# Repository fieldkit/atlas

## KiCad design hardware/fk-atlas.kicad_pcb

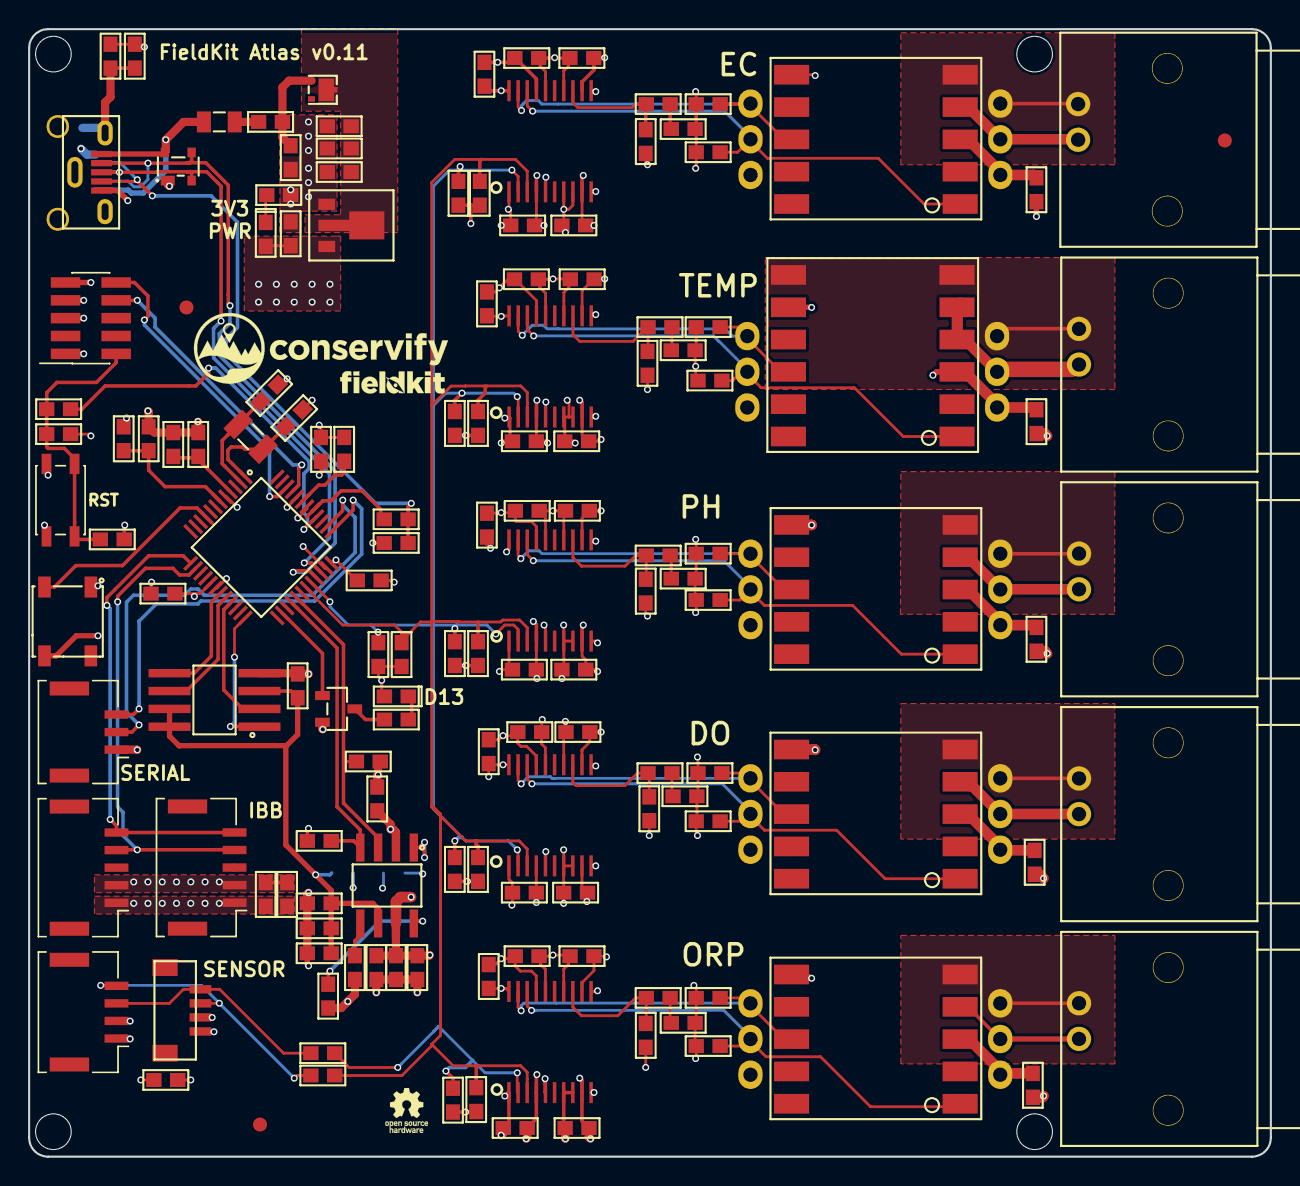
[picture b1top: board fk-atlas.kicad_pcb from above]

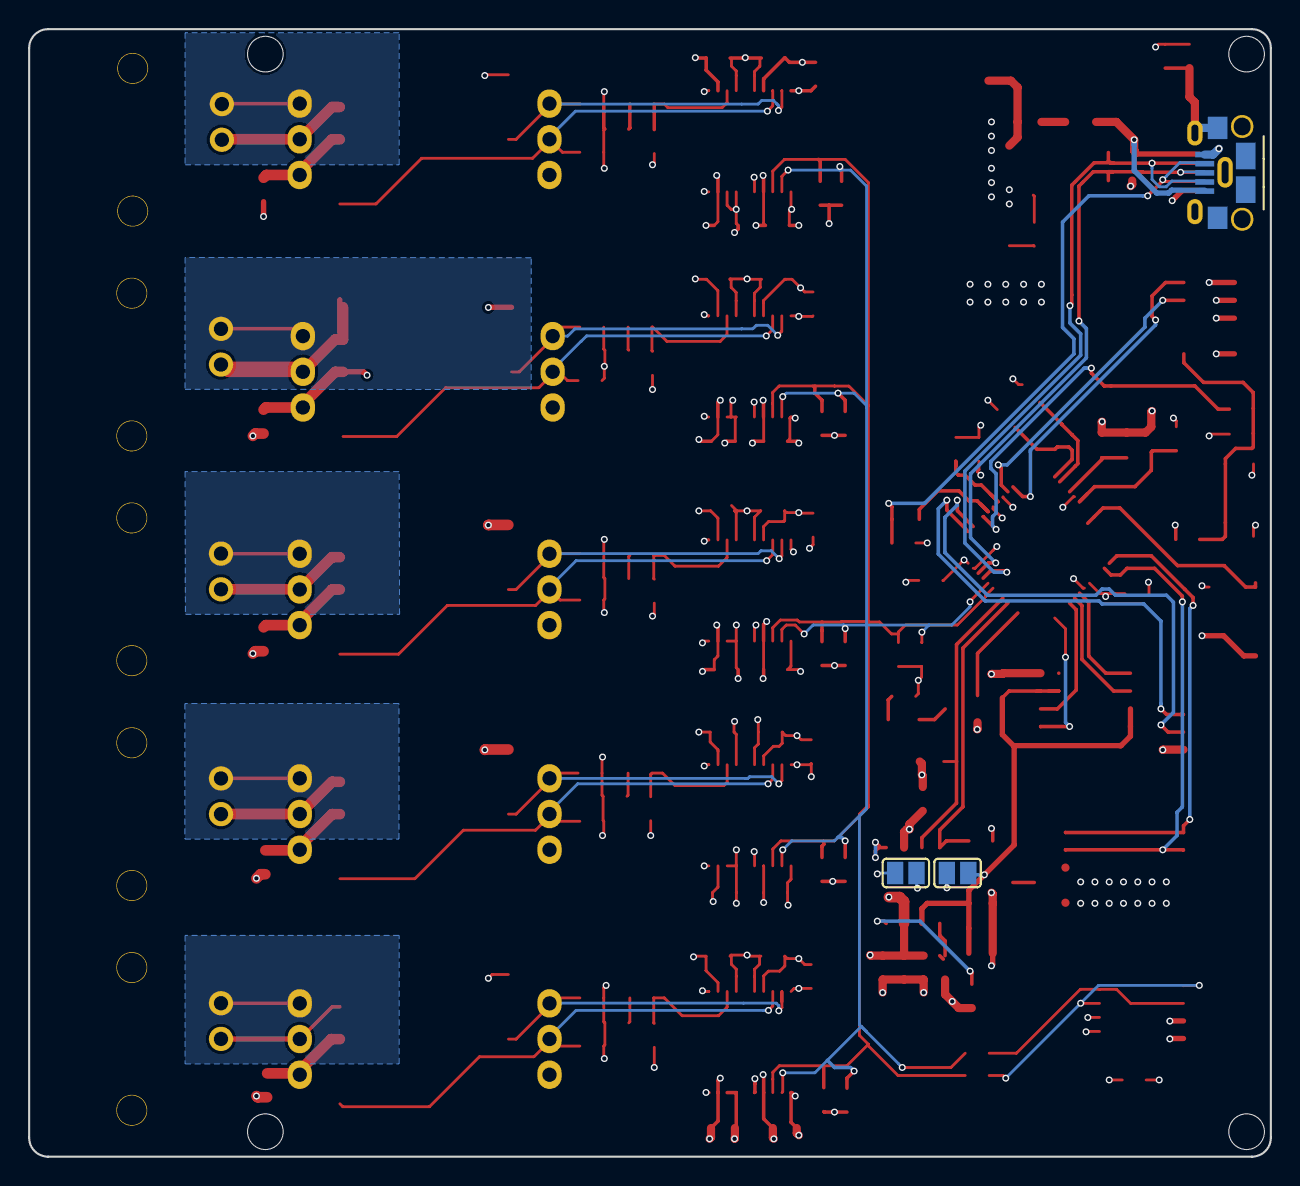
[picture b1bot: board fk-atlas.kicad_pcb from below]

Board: 4 copper layers, 88.4 x 80.3 mm, 159 parts (3 on the bottom side), 83 nets.

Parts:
C1, C10, C12: 4.7uF; CAP-0603
C2, C5, C7, C8, C9, C16, C17, C18, C20, C24, C25, C201, C203, C204, C301, C303, C304, C401, C403, C404, C501, C503, C504, C601, C603, C604: 100nF; CAP-0603
C3, C4: 18pF; CAP-0603
C6, C11, C14, C15: 1uF; CAP-0603
C13: 4.7nF; CAP-0603
C19, C21, C22, C23, C202, C205, C206, C302, C305, C306, C402, C405, C406, C502, C505, C506, C602, C605, C606: 10uF; CAP-0603
D1: Green; LED-0603
D4: Orange; LED-0603
D5: PRTR5V0U2X; SOT-143B
D6: PMEG3020CPA; SOT-1016
F1: MF-PSMF050X-2; MF-PSMF020X
J1: CONN_02x05_SWD; HDR_02x05_Pitch1.27mm_SMD_SWD
J2: MICRO-USB-VERT-TOP; USB_1051330011
J3, J8: CONN_01x02; SJ_OPEN
J4: CONN_01x03_SERIAL; Molex_CLIK-Mate_502382-0370_1x03_P1.25mm_Vertical
J5, J7: CONN_01x05; Molex_CLIK-Mate_502382-0570_1x05_P1.25mm_Vertical
J6: CONN_01x04; Molex_CLIK-Mate_502382-0470_1x04_P1.25mm_Vertical
J9: MICRO-USB-HORIZ-BOTTOM; USB_10118193-0001LF-core-mod
J10: CONN_01x04; BM04B-SRSS-TB
J201, J301, J401, J501, J601: CONN_01X02; BNC
L1, L2: BLM18KG221SN1D; IND-0603
M1, M2, M3, M4: MOUNT_HOLE; HOLE_NPTH_2.54MM
M5, M6, M7: FIDUCIAL; FIDUCIAL-1MM
P2: ATLAS_EC_PROBE; Dummy_Empty
P3: ATLAS_RTD_PROBE; Dummy_Empty
P4: ATLAS_PH_PROBE; Dummy_Empty
P5: ATLAS_DO_PROBE; Dummy_Empty
P6: ATLAS_ORP_PROBE; Dummy_Empty
Q4: 2N7002LT1G; SOT-23
R1, R7, R12: 10K; RES-0603
R2, R9: 330R; RES-0603
R3, R6: ?; RES-0603
R4, R5, R18, R19, R20, R21, R22, R23, R24, R25, R26, R27, R203, R205, R303, R305, R403, R405, R503, R505, R603, R605: 4.7K; RES-0603
R8, R13, R14: 100K; RES-0603
R10: 1M; RES-0603
R11, R17: 2K2; RES-0603
R15, R16: 0; RES-0603
R201, R202, R204, R301, R302, R304, R401, R402, R404, R501, R502, R504, R601, R602, R604: 1.5K; RES-0603
SW1: SPNO; SW_SPST_WURTH_1
U1: S25FL116K0XMFI041; SOIC-8-N-WIDE
U2: ATSAMD21G18A-AU; TQFP-48_7x7mm_Pitch0.5mm
U3: MCP1700T-3302E/MB; SOT-89
U4: TPS2052B; SOIC-8-N
U5: SK6812
U201, U301, U401, U501, U601: ADM3260; SSOP20-53
U202: ATLAS_EC; ATLAS_SENSOR_BOARD_COMBO
U302: ATLAS_RTD; ATLAS_SENSOR_BOARD_RTD_COMBO
U402: ATLAS_PH; ATLAS_SENSOR_BOARD_COMBO
U502: ATLAS_DO; ATLAS_SENSOR_BOARD_COMBO
U602: ATLAS_ORP; ATLAS_SENSOR_BOARD_COMBO
Y1: FC-135; ABS07

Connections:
3V3: C5.1, C8.1, C9.1, C15.1, C17.1, C22.1, C23.1, C24.2, D1.2, D4.2, J1.9, J3.1, J5.1, J6.1, J7.1, J8.1, J10.2, L1.2, R1.1, R4.2, R5.1, R7.2, R8.2, R12.2, U2.17, U2.36, U2.44, U3.3, U4.2, U5.3
5V0: C10.1, D6.1, L2.1
/A3: U2.9, U5.2
/D5_FLASH_CS: U1.1, U2.24
/D6_ATLAS_EN: R3.1, U2.29, U4.3
/D12_PERIPH_EN: R6.1, U2.28, U4.4
/D13: Q4.1, U2.26
/D30: J4.3, U2.37
/D31: J4.2, U2.38
/MISO: U1.2, U2.21
/MOSI: U1.5, U2.19
/PERIPH_3V3: C16.1, C20.1, C21.1, J3.2, R13.1, U1.3, U1.7, U1.8, U4.6
/RESET: R2.1, U2.40
/RST: C25.2, J1.2, R1.2, R2.2, SW1.2
/SCK: U1.6, U2.20
/SCL1: R4.1, R16.2, R19.2, R21.2, R22.2, R24.2, R26.2, U2.32, U201.2, U301.2, U401.2, U501.2, U601.2
/SCL2: J6.3, J10.4, R16.1
/SCL3: J5.4, J7.4, U2.14
/SDA1: R5.2, R15.2, R18.2, R20.2, R23.2, R25.2, R27.2, U2.31, U201.3, U301.3, U401.3, U501.3, U601.3
/SDA2: J6.4, J10.3, R15.1
/SDA3: J5.5, J7.5, U2.13
/SWCLK: J1.8, U2.45
/SWDIO: J1.10, U2.46
/USB+: D5.2, J2.3, J9.3, U2.34
/USB-: D5.3, J2.2, J9.2, U2.33
/USB_ID: R9.2, U2.41
/isolated_atlas0/EC_PGND: J201.1, U202.6
/isolated_atlas0/ISO_GND: C203.1, C204.1, C205.1, C206.1, R201.2, U201.11, U201.14, U201.16, U201.20, U202.4
/isolated_atlas0/ISO_SCL: R203.1, U201.19, U202.1
/isolated_atlas0/ISO_SDA: R205.1, U201.18, U202.2
/isolated_atlas0/ISO_VCC: C203.2, C204.2, C205.2, C206.2, R203.2, R204.2, R205.2, U201.12, U201.17, U202.3
/isolated_atlas1/ISO_GND: C303.1, C304.1, C305.1, C306.1, R301.2, U301.11, U301.14, U301.16, U301.20, U302.4
/isolated_atlas1/ISO_SCL: R303.1, U301.19, U302.1
/isolated_atlas1/ISO_SDA: R305.1, U301.18, U302.2
/isolated_atlas1/ISO_VCC: C303.2, C304.2, C305.2, C306.2, R303.2, R304.2, R305.2, U301.12, U301.17, U302.3
/isolated_atlas1/RTD_PGND: J301.1, U302.6
/isolated_atlas2/ISO_GND: C403.1, C404.1, C405.1, C406.1, R401.2, U401.11, U401.14, U401.16, U401.20, U402.4
/isolated_atlas2/ISO_SCL: R403.1, U401.19, U402.1
/isolated_atlas2/ISO_SDA: R405.1, U401.18, U402.2
/isolated_atlas2/ISO_VCC: C403.2, C404.2, C405.2, C406.2, R403.2, R404.2, R405.2, U401.12, U401.17, U402.3
/isolated_atlas2/PH_PGND: J401.1, U402.6
/isolated_atlas3/DO_PGND: J501.1, U502.6
/isolated_atlas3/ISO_GND: C503.1, C504.1, C505.1, C506.1, R501.2, U501.11, U501.14, U501.16, U501.20, U502.4
/isolated_atlas3/ISO_SCL: R503.1, U501.19, U502.1
/isolated_atlas3/ISO_SDA: R505.1, U501.18, U502.2
/isolated_atlas3/ISO_VCC: C503.2, C504.2, C505.2, C506.2, R503.2, R504.2, R505.2, U501.12, U501.17, U502.3
/isolated_atlas4/ISO_GND: C603.1, C604.1, C605.1, C606.1, R601.2, U601.11, U601.14, U601.16, U601.20, U602.4
/isolated_atlas4/ISO_SCL: R603.1, U601.19, U602.1
/isolated_atlas4/ISO_SDA: R605.1, U601.18, U602.2
/isolated_atlas4/ISO_VCC: C603.2, C604.2, C605.2, C606.2, R603.2, R604.2, R605.2, U601.12, U601.17, U602.3
/isolated_atlas4/ORP_PGND: J601.1, U602.6
GND: C1.2, C2.2, C3.1, C4.1, C5.2, C6.2, C7.2, C8.2, C9.2, C10.2, C11.1, C12.2, C13.2, C14.2, C15.2, C16.2, C17.2, C18.2, C19.2, C20.2, C21.2, C22.2, C23.2, C24.1, C25.1, C201.2, C202.2, C301.2, C302.2, C401.2, C402.2, C501.2, C502.2, C601.2, C602.2, D5.1, J1.1, J1.5, J1.7, J2.5, J4.1, J5.2, J6.2, J7.2, J9.5, J10.1, Q4.2, R3.2, R6.2, R10.2, R13.2, R14.2, R17.2, SW1.1, U1.4, U2.5, U2.18, U2.35, U2.42, U3.1, U4.1, U5.1, U201.1, U201.5, U201.7, U201.8, U201.10, U301.1, U301.5, U301.7, U301.8, U301.10, U401.1, U401.5, U401.7, U401.8, U401.10, U501.1, U501.5, U501.7, U501.8, U501.10, U601.1, U601.5, U601.7, U601.8, U601.10
unnamed: C1.1, C2.1, U2.4
unnamed: C3.2, U2.2, Y1.1
unnamed: C4.2, U2.1, Y1.2
unnamed: C6.1, U2.43
unnamed: C7.1, L1.1, U2.6
unnamed: C13.1, J2.6, J9.7, R10.1
unnamed: D1.1, R17.1
unnamed: D4.1, R11.1
unnamed: F1.1, L2.2
unnamed: J2.4, J9.4, R8.1, R9.1
unnamed: J201.2, U202.5
unnamed: J301.2, U302.5
unnamed: J401.2, U402.5
unnamed: J501.2, U502.5
unnamed: J601.2, U602.5
unnamed: Q4.3, R11.2
unnamed: R7.1, U4.5
unnamed: R12.1, U4.8
unnamed: R201.1, R202.1, U201.13
unnamed: R202.2, R204.1
unnamed: R301.1, R302.1, U301.13
unnamed: R302.2, R304.1
unnamed: R401.1, R402.1, U401.13
unnamed: R402.2, R404.1
unnamed: R501.1, R502.1, U501.13
unnamed: R502.2, R504.1
unnamed: R601.1, R602.1, U601.13
unnamed: R602.2, R604.1
VBUS: C11.2, C12.1, C14.1, D6.3, U3.2
VCC: C18.1, C19.1, C201.1, C202.1, C301.1, C302.1, C401.1, C402.1, C501.1, C502.1, C601.1, C602.1, J8.2, R14.1, R18.1, R19.1, R20.1, R21.1, R22.1, R23.1, R24.1, R25.1, R26.1, R27.1, U4.7, U201.4, U201.9, U301.4, U301.9, U401.4, U401.9, U501.4, U501.9, U601.4, U601.9
VUSB: D5.4, F1.2, J2.1, J9.1

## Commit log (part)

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2017-03-13 First pass at the atlas sensor.
2017-03-13 Labels and logos.
2017-03-13 Some alignment tweaks.
2017-03-13 More tweaks, alignment and trace widths here and there.
2017-03-13 Cosmetic stuff, removing a random old trace.
2017-03-13 Labels and cosmetics.
2017-03-13 Oops, S2 has to be isolated GND.
2017-03-15 Adding water temp header and labels. Bump revision.
2017-06-26 Starting on atlas module. Full isolation using adm3260.
2017-06-26 Making a little more room for the BNCs, just in case.
2017-08-25 Adding an MCU, gonna send away for these to start testing.
2017-09-12 Export new gerbers.
2017-09-26 Fix SSOP-20 width on the isolator.
2017-09-27 Adding a D13 LED to the on board MCU.
2017-09-27 Fix hole diameters.
2017-09-27 Fix USB drills.
2017-09-27 Make part labels easy to read for assembly.
2017-09-30 Individual atlas sensor values for costing.
2017-09-30 Normalizing some passive footprints.
2017-10-02 Adding placeholders for probes for the BOM.
2017-10-06 Add footprint for OEM Atlas Circuit.
2017-10-06 Use SSOP20 with narrow pads.
2017-10-09 Tweak BNC footprint. Plot gerbers.
2017-10-09 Very basic test firmware for checking each sensor board
2017-11-01 Move labels/references/values around for assembly.
2017-11-02 Remove feather and pull MCU stuff in tighter.
2017-11-14 Unfortunately, can't remember what's changed here. Sorry.
2017-11-17 Break second I2C out. Add some PCB labels.
2017-11-22 Adding build files.
2017-11-23 Starting on the module firmware.
2017-11-23 Roughing in sensor module firmware.
2017-11-24 Move code out of headers.
2017-11-24 Fully parallel Atlas reading.
2017-11-24 Working on comms, still some oddities.
    Tried adding a STATUS read and not getting data back reliable.
2017-11-26 Fixing warnings.
2017-11-26 Some interface cleanup, tweaks. Nothing substantial.
2017-11-26 Use enum for Atlas response code.
2017-11-26 These are gone.
2017-11-26 Deduce sensor types.
    Not too happy with how this is done, though this'll work.
2017-11-27 Slurp sensor readings up into the top module level.
2017-11-27 Get rid of SensorReader/Sensor division.
2017-11-27 Adding flash memory to the schematic.
2017-11-27 Fix the hacked sleep delay.
    This fancies up the tick return so that children can indicate they're waiting and be told when their other siblings are waiting. This should be pretty generalizable to other situations. I was trying 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
    Anyway, this hack was there because some modules seem to awaken when we're talking to others so this sleeps them all at once when we're done doing non-sleep things.
2017-11-28 Use logging from firmware-common
2017-11-28 Triggering a build.
2017-11-28 Adding flash memory to PCB.
2017-11-28 Standard on naming entry point file main.cpp
2017-11-29 Integrate TwoWire module code and atlas code.
2017-11-30 Don't sync delay so we can actually service requests.
2017-11-30 Flush I2C bus when we resume.
    After sleeping and talking to the Atlas modules there are NULs left
    over in the buffers. This gets rid of them.
2017-12-02 Adapt to new firmware.
2017-12-02 Adding app-protocol dependency. Fix this.
2017-12-03 Add WiFi dep, temporarily.
2017-12-04 Update to use friendlier ModuleInfo approach.
2017-12-04 Rename ExampleModule to AtlasModule.
2017-12-04 Re-use Makefile patterns.
2017-12-09 Add ASFcore dependency.
2017-12-13 Fix warnings from printf enforcement.
2017-12-19 Add enable flag toggling, though this hardware wise isn't working.
2017-12-20 Convert atlas enable to low side switch.
2017-12-22 Remove obsolete method.
2017-12-22 Leds control moved to firmware-common.
2017-12-22 Update beginReading to return ModuleReadingStatus.
2017-12-27 Add AtSamd library.
2017-12-27 Renaming max1704x library to FuelGauge.
2017-12-28 Moving labels around for easier assembly.
2017-12-28 Break out Wire3 instead of Wire2.
2017-12-29 Give GND on USB a firmer connection.
2017-12-31 Adding TinyGPS library.
2017-12-31 Change to PendingReading struct.
2018-01-11 Use logging with facility.
2018-01-11 Pass which TwoWire to use for core comms.
2018-01-11 Move into fk namespace.
2018-01-11 Use TwoWire from FK firmware code.
2018-01-11 Adding a Vin so we can provide an unregulated voltage.
2018-01-11 Add labels for LEDs
2018-01-11 Add LED labels, make room for mounting in one corner.
2018-01-18 Add data-protocol dependency.
2018-01-18 Fix label ordering on readings.
2018-02-13 Use adafruit ASFcore
2018-02-16 Use forked WiFi101 library.
2018-02-16 SerialFlash version/dependency.
2018-02-17 Adding the basic Atlas specific protocol.
2018-02-17 Working out the initial custom commands details.
2018-02-17 Move pool to parent and allocate data from there, for now.
2018-02-17 Fix order.
2018-02-18 Move more code into AtlasModule, cleanup some problematic code.
2018-02-18 Constant for timeout on custom commands.
2018-02-19 Use static pool.
2018-02-20 Fix protocol's package.json
2018-02-20 Order was right the first time.
2018-03-05 Using key names for sensors. Going to pretty up using metadata.
2018-03-09 Fix TDS sensor name.
2018-03-14 Log message tweak.
2018-04-03 Set module type.
2018-04-19 Friendlier sensors task. Use supervisor for ephemeral tasks.
2018-04-27 Add lwstreams dependency.
2018-04-27 Project name, disable verbose makefile.
2018-05-04 Adding mounting holes for Atlas.
2018-05-07 Flash memory is on PERIPH_GND now too.
2018-05-21 Updating BOM details.
2018-06-18 Adding fiducials.
2018-06-18 Silkscreen tweaks.
2018-06-18 Plot gerbers.
2018-06-27 Add phylum dependency.
2018-06-29 Adjust pad mask clearance to avoid exposing ground plane.
2018-07-03 Add dimensions.
2018-07-06 Toggle enable pin.
2018-07-06 High side switch on peripherals.
2018-07-10 Plotting gerbers.
2018-07-10 Don't enable LEDs after configurable uptime.
2018-07-18 Clear values. Just in case.
2018-07-18 Enable peripherals when taking readings.
2018-07-18 Module comms are on a different TwoWire now.
2018-07-18 Allow ORP to be disabled, for the Amazon project.
2018-07-18 Add MS5803 pressure sensor configuration.
2018-07-19 Longer backoff if we have to power on the sensors.
2018-07-19 Apply temperature compenstation.
2018-07-20 Amazon build script.
2018-07-24 Fix load switch part.
2018-07-24 Add lwcron dependency.
2018-07-25 Pass firmware/build info in.
2018-07-25 Upgrade to Kicad 5.
2018-07-30 Use latest dependencies.
2018-07-30 Generate multiple binaries with different configurations.
2018-07-30 Some minor cleanup. Regenerate gerbers.
2018-07-30 Add number of readings and module name to info.
2018-07-31 Use new allocation strategy for ModuleInfo.
2018-08-01 Move protocol to its own repository.
2018-08-02 Ignore dependencies.cmake
2018-08-03 Add Jenkinsfile.
2018-08-08 Trigger distribution job.
2018-08-09 Not waiting on distribution build.
2018-08-09 Use helper for updating distribution site.
2018-08-11 Compile flags to enable flash in phylum.
2018-08-13 Disable peripheral shutdown for now.
2018-08-14 Add distribute step.
2018-08-15 Archive binaries.
2018-08-15 Use smaller Task include.
2018-08-20 Set firmware compiled time.
2018-08-21 Switch to newer Arduino CMake build.
2018-08-21 Pass archive pathspec.
2018-08-21 Set firmware directory.
2018-08-22 Consistent part values across our schematics.
2018-08-24 Use repository URLs for deps.
2018-08-24 Use tools name for dependencies.sd.
2018-08-24 Fix Sk6812 and include pins in signal names.
2018-08-24 Fix DRC in schematic mode.
2018-08-28 Starting the migration to use states instead of callbacks.
2018-08-28 Use more compatible FP for flash.
2018-08-28 Consistency in part values
2018-08-28 Add NeoPixel dependency.
2018-09-07 Bump version and plot gerbers.
2018-09-26 Pin to newer library versions.
2018-09-27 Specify flash state struct.
2018-09-27 Start support for testing OEM based boards.
2018-09-28 New footprint for the Atlas RTD OEM board.
2018-10-04 Give module code pin to control flash power.
2018-10-05 Separate custom queries and some FSM stuff into their own files.
2018-10-05 Major refactor to fix Custom queries.
    These are handled by a separate task now and done a little more asynchronously
    and so stuff had to move around. This also marks the beginning of the removal of
    the unnecessary Sensor abstraction that just didn't turn into anything more
    useful. I think for Atlas in particular we just focus on something concise.
    There isn't a huge value in generalizing this stuff.
2018-10-05 Initialize sensors at startup.
2018-10-05 Power on sensors when we need them and power off after inactivity.
2018-10-05 Split up more files.
2018-10-05 Rename SensorPower class.
2018-10-05 Move the old initialize step into the module configuration state.
2018-10-07 Use new led disable after configuration value.
2018-10-19 Reboot device if we're failing to get expected number of readings.
    This is a fail safe for a misconfigured EC board, primarily.
2018-10-19 Set probe type, for now this is easier testing wise.
2018-10-22 Don't keep retrying Atlas comms forever. Set a cap.
    FK-487
2018-10-22 Longer delay when Atlas isn't ready.
2018-10-31 Query for protocol lock and lock after. Retry sends on errors.
2018-10-31 Set minimum on time for peripherals.
    This is to avoid accidentally erasing atlas module EEPROM memory by power
    cycling them too quickly.
2018-10-31 Configure runs async so we can respond to queries at startup.
    This uses the new ModuleHooks so that sensors and the power controls are
    serviced normally. Also reworks the power code so that we power off the sensors
    at a fixed interval after we've stopped using them.
2018-10-31 Open debug serial if USB is unavailable.
2018-10-31 Fix retries when configuring EC parameters.
2018-10-31 Separate power control for Atlas from Flash. Add pull downs.
2018-11-01 Set required uptime parameter.
2018-11-07 Adding some pull downs.
2018-11-19 Moving labels around.
2018-11-20 Annotate which Atlas pads to solder.
2018-11-24 Enable Atlas modules for boards with TPS2052.
2018-11-24 Configure probe type for EC in test firmware.
2018-11-24 Default to prototype boards, for now.
2018-11-28 Adding calibration firmware skeleton.
2018-11-28 Very basic calibration firmware. Basically a REPL utility.
2018-11-30 Drop prototype Atlas modules - focus on getting OEM boards working.
2018-11-30 Mounting holes are 2.7mm. Plotting.
2018-12-04 Add orientation indicator to SWD fp.
2018-12-11 Report probe type after we set it.
2018-12-11 Disable sensor I2C when we disable sensor power.
2018-12-11 Pull peripheral enable/disable into one place.
2018-12-12 Fix make jobserver warnings.
2018-12-12 Use plain BoardConfig, start renaming and moving before OEM support.
2018-12-12 Custom AtlasBoard that exposes Atlas sensor powering.
2018-12-12 Use new PowerSwitch and Board for controlling atlas sensor modules.
2018-12-12 Started transition to 4 layer board
2018-12-12 Rename SensorModule to AtlasSensorCollection.
2018-12-13 Rename and start the split to support both EZO and OEM boards.
2018-12-13 Changed the spacing on all ground and power planes for better isolation
2018-12-13 Moving implementation details into EzoAtlas.
2018-12-13 Fix power switch turning on when checked. Enable in take readings.
2018-12-13 Use a type alias to select sensor type.
    We won't need runtime selection for this.
2018-12-13 Swapped out the USB connectors and added a second connector for the 'sensor' using the qwiic connector
2018-12-13 Removed VIN connection
2018-12-13 Added a power indicator LED, finished touching up traces and added logos, markings back in
2018-12-13 Added pull up resistors and a debounce cap for the reset button
2018-12-13 Generated gerbers for v0.11
2018-12-13 Fix board name on silk.
2018-12-14 Actually return values when using OEM sensors.
2018-12-14 Blink LEDs during sensor readings.
2018-12-14 Only wake once if we're hibernating.
2018-12-14 Dropping old delays, don't seem to be necessary.
2019-01-02 Generated panelized version of v0.11, including gerbers
2019-01-07 Cleaned up old gerber files and regenerated panelized gerbers and original file after fab found an unconnected track (A2, wasn't used for anything)
2019-02-18 Use board definition in calibration script.
2019-02-18 Flash and open up calibration terminal.
2019-02-19 Adding a 1413.0us calibration command.
2019-02-19 Build Amazon w/o ORP.
2019-02-19 Archive test firmware.
2019-02-25 Upgrade nanopb.
2019-03-13 Fixed missing resistor values.
2019-04-23 Use absolute BUILD in Makefile.
2019-04-23 A much improved calibration flashing script.
2019-04-23 Fix testing code logic :/ Add a timer feature to calib firmware.
